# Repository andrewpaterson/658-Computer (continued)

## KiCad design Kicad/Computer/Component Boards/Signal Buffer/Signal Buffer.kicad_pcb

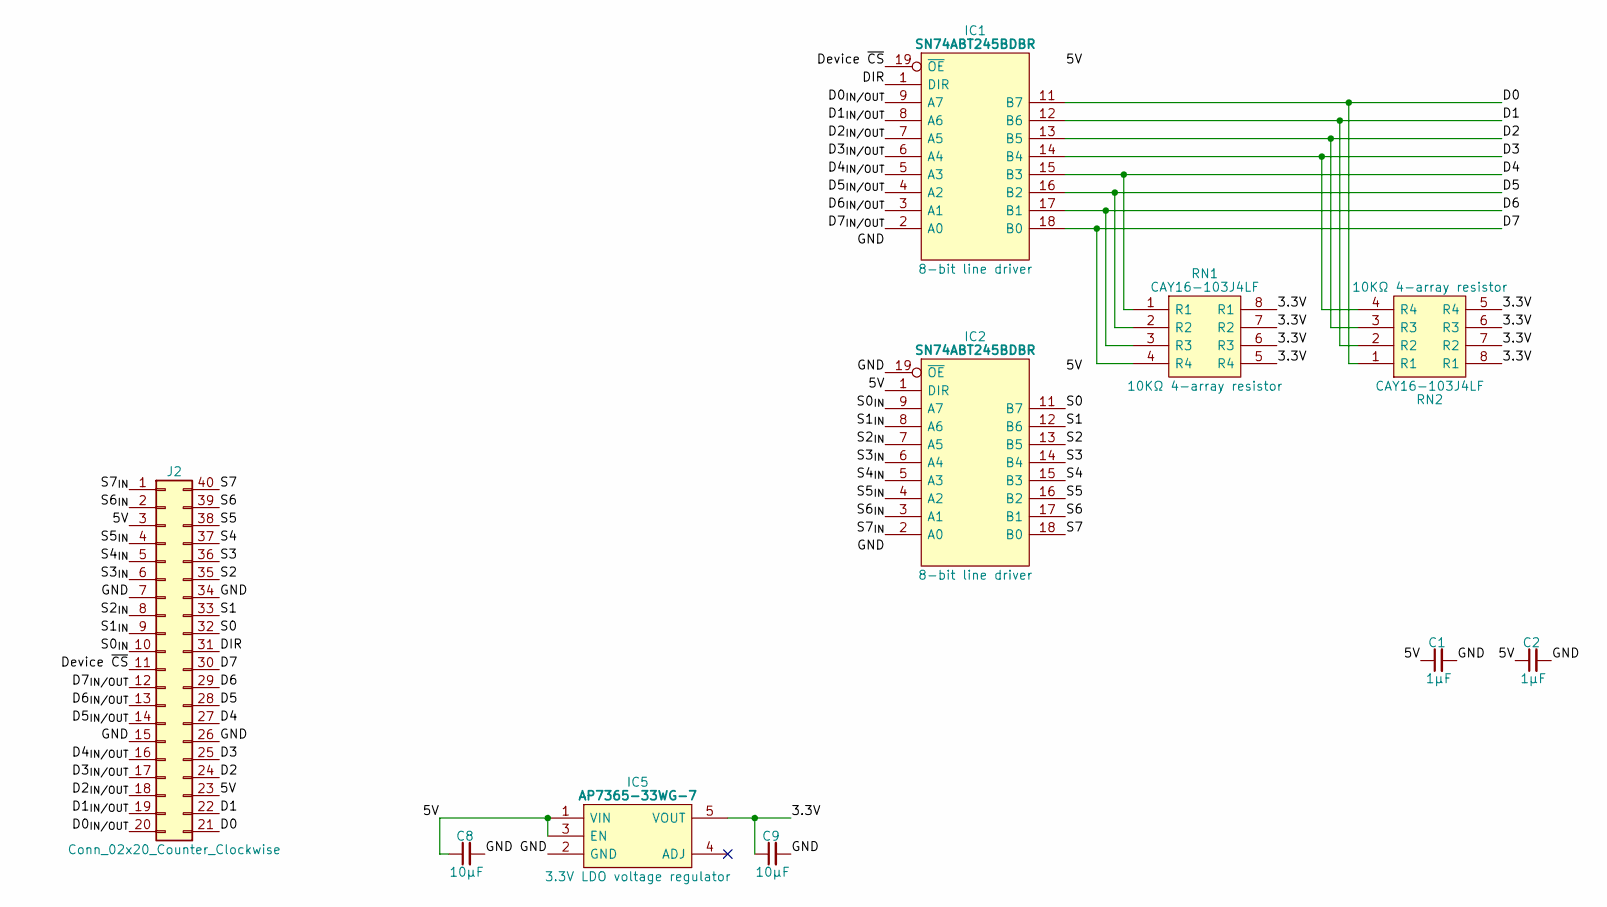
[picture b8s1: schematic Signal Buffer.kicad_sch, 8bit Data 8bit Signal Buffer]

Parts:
C1, C2: 1μF; C_0805
C8, C9: 10µF; C_0805
IC1, IC2: SN74ABT245BDBR; SOP65P780X200-20N; Manufacturer_Part_Number SN74ABT245BDBR; Mouser Part Number 595-SN74ABT245BDBR
IC5: AP7365-33WG-7; SOT95P285X130-5N; Manufacturer_Part_Number AP7365-33WG-7; Mouser Part Number 621-AP7365-33WG-7
J2: Conn_02x20_Counter_Clockwise; DIP-40_Board_W15.24mm
RN1, RN2: CAY16-103J4LF; CAY16-J4; Manufacturer_Part_Number CAY16-103J4LF; Mouser Part Number 652-CAY16-103J4LF

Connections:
/3.3V: C9.1, IC5.5 (VOUT), RN1.5 (R4), RN1.6 (R3), RN1.7 (R2), RN1.8 (R1), RN2.5 (R4), RN2.6 (R3), RN2.7 (R2), RN2.8 (R1)
/5V: C1.1, C2.1, C8.1, IC1.20 (5V), IC2.1 (DIR), IC2.20 (5V), IC5.1 (VIN), IC5.3 (EN), J2.3, J2.23
/D0: IC1.11 (B7), J2.21, RN2.1 (R1)
/D0_{IN/OUT}: IC1.9 (A7), J2.20
/D1: IC1.12 (B6), J2.22, RN2.2 (R2)
/D1_{IN/OUT}: IC1.8 (A6), J2.19
/D2: IC1.13 (B5), J2.24, RN2.3 (R3)
/D2_{IN/OUT}: IC1.7 (A5), J2.18
/D3: IC1.14 (B4), J2.25, RN2.4 (R4)
/D3_{IN/OUT}: IC1.6 (A4), J2.17
/D4: IC1.15 (B3), J2.27, RN1.1 (R1)
/D4_{IN/OUT}: IC1.5 (A3), J2.16
/D5: IC1.16 (B2), J2.28, RN1.2 (R2)
/D5_{IN/OUT}: IC1.4 (A2), J2.14
/D6: IC1.17 (B1), J2.29, RN1.3 (R3)
/D6_{IN/OUT}: IC1.3 (A1), J2.13
/D7: IC1.18 (B0), J2.30, RN1.4 (R4)
/D7_{IN/OUT}: IC1.2 (A0), J2.12
/DIR: IC1.1 (DIR), J2.31
/Device ~CS: IC1.19 (~OE), J2.11
/GND: C1.2, C2.2, C8.2, C9.2, IC1.10 (GND), IC2.10 (GND), IC2.19 (~OE), IC5.2 (GND), J2.7, J2.15, J2.26, J2.34
/S0: IC2.11 (B7), J2.32
/S0_{IN}: IC2.9 (A7), J2.10
/S1: IC2.12 (B6), J2.33
/S1_{IN}: IC2.8 (A6), J2.9
/S2: IC2.13 (B5), J2.35
/S2_{IN}: IC2.7 (A5), J2.8
/S3: IC2.14 (B4), J2.36
/S3_{IN}: IC2.6 (A4), J2.6
/S4: IC2.15 (B3), J2.37
/S4_{IN}: IC2.5 (A3), J2.5
/S5: IC2.16 (B2), J2.38
/S5_{IN}: IC2.4 (A2), J2.4
/S6: IC2.17 (B1), J2.39
/S6_{IN}: IC2.3 (A1), J2.2
/S7: IC2.18 (B0), J2.40
/S7_{IN}: IC2.2 (A0), J2.1

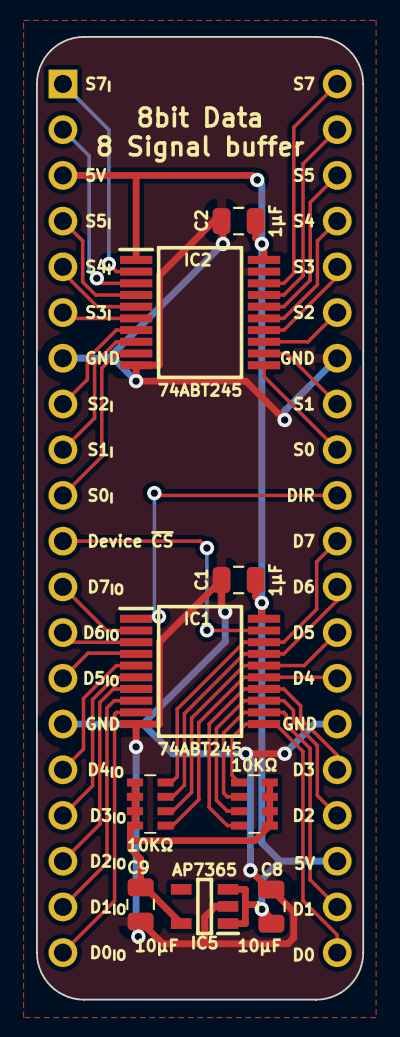
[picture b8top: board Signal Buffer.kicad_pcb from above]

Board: 2 copper layers, 18.1 x 53.5 mm, 10 parts (0 on the bottom side), 37 nets.
